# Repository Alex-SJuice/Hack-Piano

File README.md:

# Hack Piano

A macropad, in the form of a piano!

It can serve as a normal macropad too.

Made through [Hackpad](https://hackpad.hackclub.com/) and Stardance, hosted by [Hackclub](https://hackclub.com/)!

[Showcase](https://youtu.be/vqTRjgcmdTU)

## Motivation

I've wanted a MIDI keyboard for a while, and I thought this would be a decent substitute (and a fun challenge!).

This is my first ever hardware project I've made from start to finish, with my own design, so It's very exciting!

I'm hoping to use the skills from this project in others, like my WIP 3d camera (shameless plug)

## Features

 - 12 MX-style keys arranged like a piano
 -  programmable rotary encoder
 - 0.91" OLED screen

## Schematic & PCB

It was difficult to align everything so the traces are nice, especially since I was forced to wire the keys in a 4x3 grid because of the number of pins

Another BIG problem was that the pcb was too wide. I decided to split the pcb in half and stack the two halves together to get the size requirements, then add breakpoints so I could assemble and solder the pcb together. Thanks to Anicetus in the hackclub slack for the idea!

Final Shape:

## Case

Oh my goodness, the case was actually horrible to work on. It mostly stems from the fact that I decided to make a bunch of small details that would be really annoying to change if say, the lid and base were different shapes the entire time. Also someone's got to burn the Onshape splines on a stake.

## BOM:
 - 12x Cherry MX Switches
 - 12x DSA Keycaps (optional but you can get 2u keys for the bottoms 7)
 - 4x M3x5x4 Heatset inserts
 - 4x M3x16mm screws
 - 12x 1N4148 DO-35 Diodes
 - 1x 0.91" 128x32 OLED Display
 - 1x EC11 Rotary Encoder
 - 1x XIAO RP2040
 - 1x Case (2 printed parts)

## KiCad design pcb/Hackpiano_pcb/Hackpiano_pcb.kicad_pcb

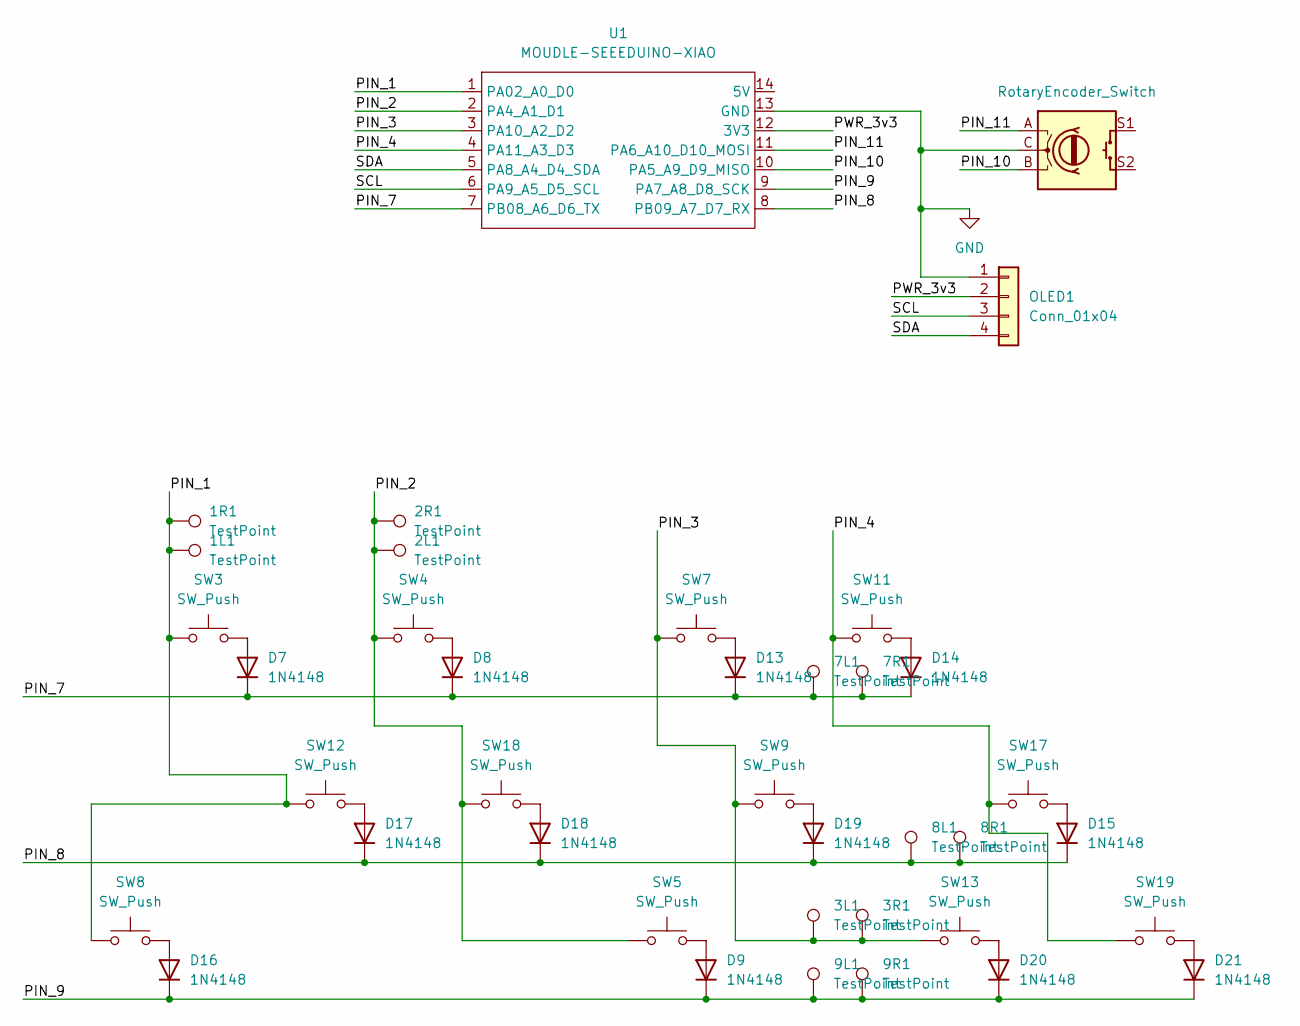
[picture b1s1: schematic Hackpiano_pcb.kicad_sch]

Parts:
1L1, 1R1, 2L1, 2R1, 3L1, 3R1, 7L1, 7R1, 8L1, 8R1, 9L1, 9R1: TestPoint; TestPoint_Pad_D1.0mm
D7, D8, D9, D13, D14, D15, D16, D17, D18, D19, D20, D21: 1N4148; D_DO-35_SOD27_P7.62mm_Horizontal
OLED1: Conn_01x04; SSD1306-0.91-OLED-4pin-128x32
SW3, SW4, SW5, SW7, SW8, SW9, SW11, SW12, SW13, SW17, SW18, SW19: SW_Push; SW_Cherry_MX_1.00u_PCB
SongSelect1: RotaryEncoder_Switch; RotaryEncoder_Alps_EC11E-Switch_Vertical_H20mm
U1: MOUDLE-SEEEDUINO-XIAO; XIAO-Generic-Hybrid-14P-2.54-21X17.8MM

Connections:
/PIN_1: 1L1.1 (1_1), 1R1.1 (1_1), SW3.1, SW8.1, SW12.1, U1.1 (PA02_A0_D0)
/PIN_2: 2L1.1 (1_1), 2R1.1 (1_1), SW4.1, SW5.1, SW18.1, U1.2 (PA4_A1_D1)
/PIN_3: 3L1.1 (1_1), 3R1.1 (1_1), SW7.1, SW9.1, SW13.1, U1.3 (PA10_A2_D2)
/PIN_4: SW11.1, SW17.1, SW19.1, U1.4 (PA11_A3_D3)
/PIN_7: 7L1.1 (1_1), 7R1.1 (1_1), D7.1 (K), D8.1 (K), D13.1 (K), D14.1 (K), U1.7 (PB08_A6_D6_TX)
/PIN_8: 8L1.1 (1_1), 8R1.1 (1_1), D15.1 (K), D17.1 (K), D18.1 (K), D19.1 (K), U1.8 (PB09_A7_D7_RX)
/PIN_9: 9L1.1 (1_1), 9R1.1 (1_1), D9.1 (K), D16.1 (K), D20.1 (K), D21.1 (K), U1.9 (PA7_A8_D8_SCK)
/PIN_10: SongSelect1.B, U1.10 (PA5_A9_D9_MISO)
/PIN_11: SongSelect1.A, U1.11 (PA6_A10_D10_MOSI)
/PWR_3v3: OLED1.2, U1.12 (3V3)
/SCL: OLED1.3, U1.6 (PA9_A5_D5_SCL)
/SDA: OLED1.4, U1.5 (PA8_A4_D4_SDA)
GND: OLED1.1, SongSelect1.C, U1.13 (GND)
unnamed: D7.2 (A), SW3.2
unnamed: D8.2 (A), SW4.2
unnamed: D9.2 (A), SW5.2
unnamed: D13.2 (A), SW7.2
unnamed: D14.2 (A), SW11.2
unnamed: D15.2 (A), SW17.2
unnamed: D16.2 (A), SW8.2
unnamed: D17.2 (A), SW12.2
unnamed: D18.2 (A), SW18.2
unnamed: D19.2 (A), SW9.2
unnamed: D20.2 (A), SW13.2
unnamed: D21.2 (A), SW19.2

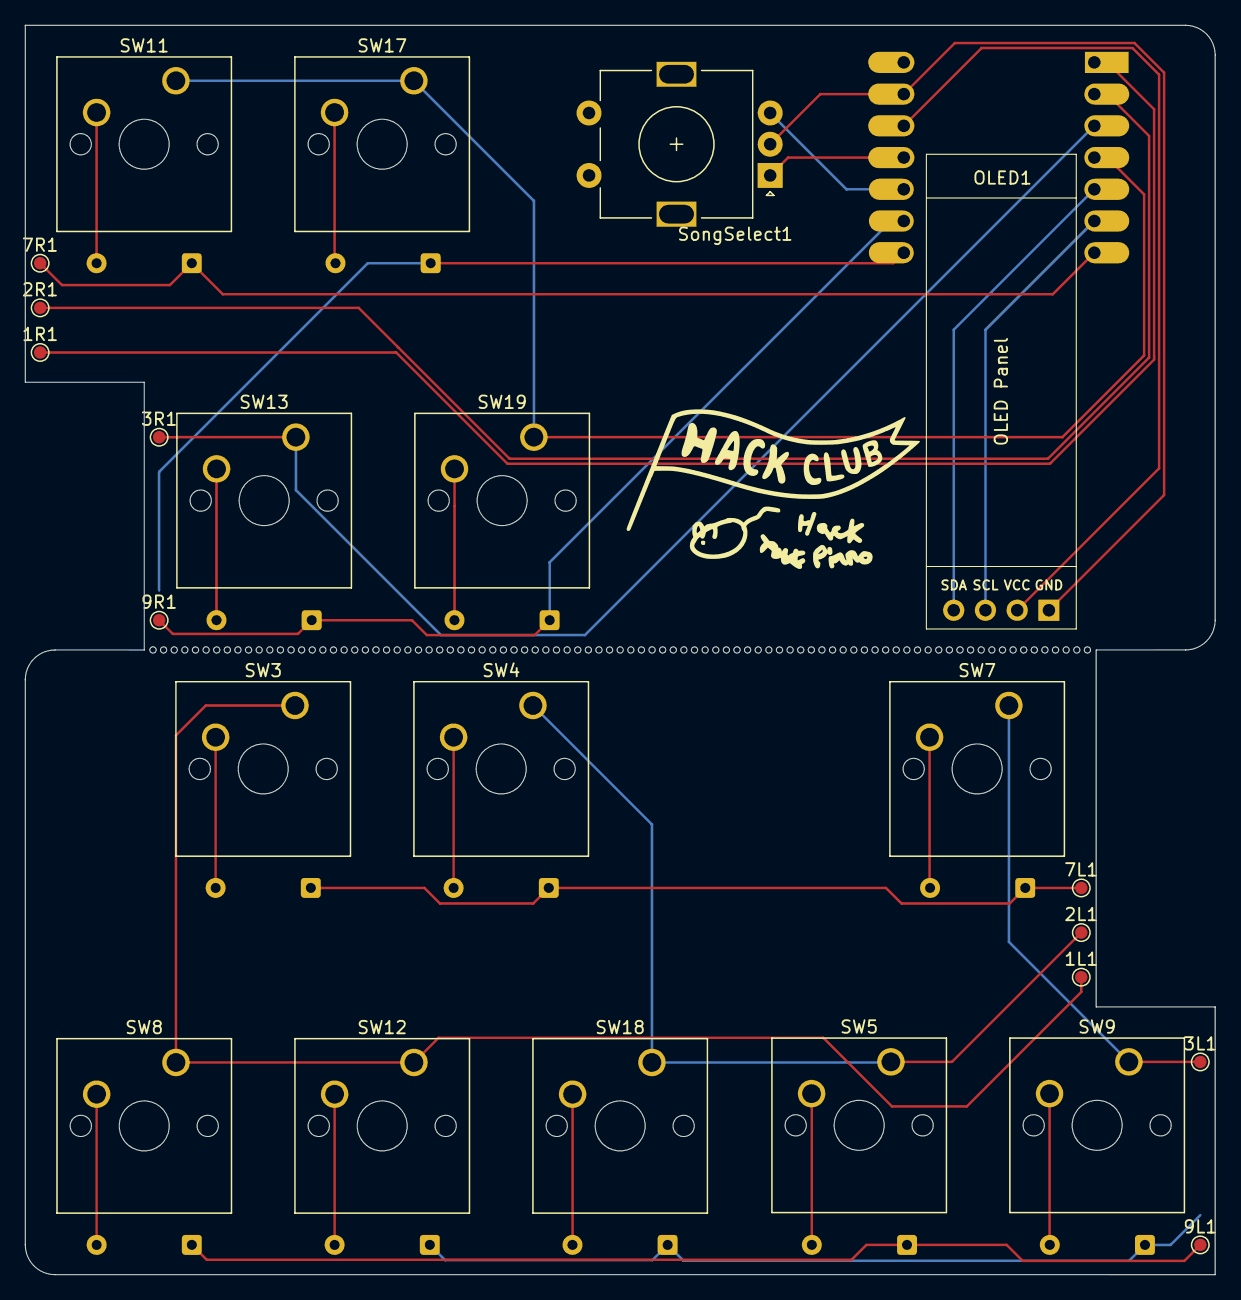
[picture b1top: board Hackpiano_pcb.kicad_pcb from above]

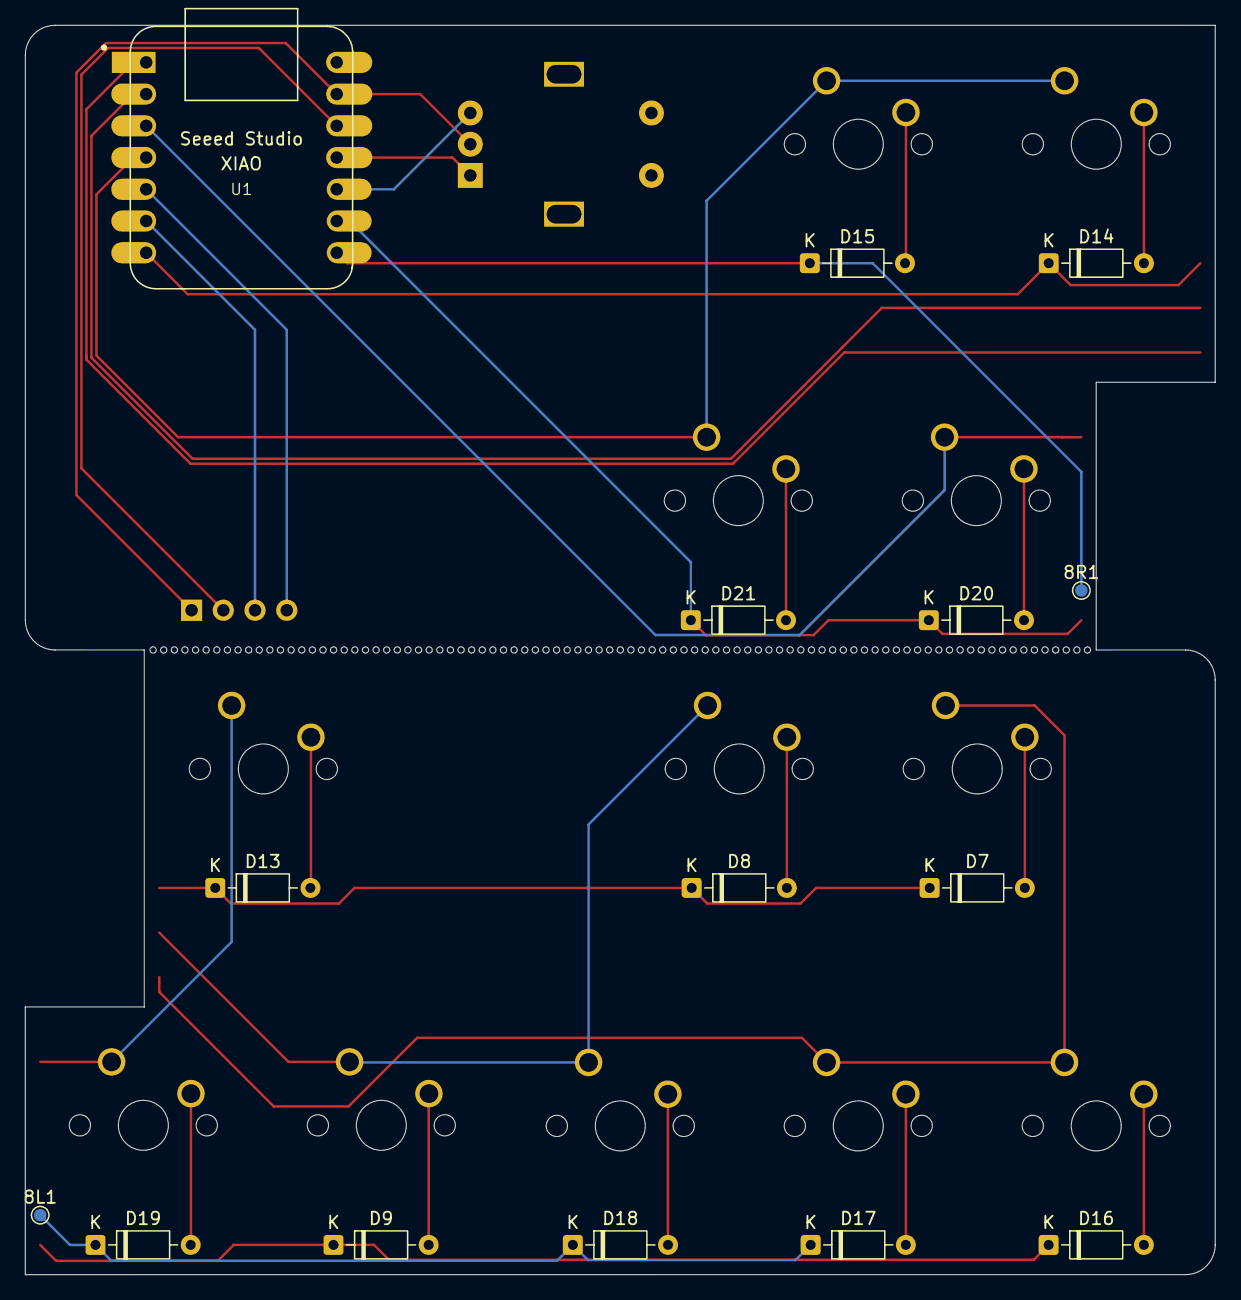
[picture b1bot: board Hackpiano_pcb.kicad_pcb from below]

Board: 2 copper layers, 95.3 x 100.0 mm, 39 parts (15 on the bottom side), 25 nets.

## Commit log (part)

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2026-06-05 setup or smth
2026-06-05 Schem done, pcb wip
2026-06-05 more pcb work
2026-06-07 pcb done
    pcb too big
    might have to scrap the project entirely
2026-06-08 new pcb design
2026-06-08 pcb done maybe
    kudos anicetus
2026-06-08 readme fix
2026-06-08 actual readme fix
2026-06-11 gerbers
    castellated holes are really expensive though so there's gonna have to be a slight redesign
2026-06-12 test pads
    no more castellated holes
    my wallet is saved
2026-06-12 forgor to save pcb
    oops
2026-06-13 after solder
    and curves :)
2026-06-13 oled centered
    with silkscreen!
2026-06-20 lots of case work
    pcb subject to change, so no gerbers yet
2026-06-23 reorganization 1
2026-06-23 partial pcb path fixes
2026-06-25 flipping diodes and stuff
2026-06-28 hopefully I'm done
    I'm so not done bro I'm gonna have to remodel this whole thing <:(((((((((((
2026-06-28 new pics
2026-06-28 forgor to move some images
2026-06-28 quick readme change
2026-06-29 gerbers i think
    bro the firmware pmo
2026-06-29 firmware (mostly)
2026-06-30 compiled firmware
